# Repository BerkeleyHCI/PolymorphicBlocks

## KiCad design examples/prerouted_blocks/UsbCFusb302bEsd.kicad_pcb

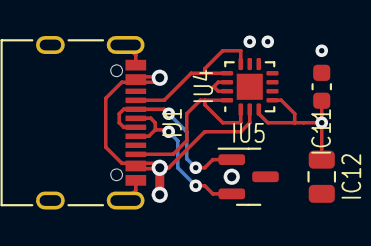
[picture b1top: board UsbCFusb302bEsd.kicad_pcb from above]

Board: 2 copper layers, 5 parts (0 on the bottom side), 8 nets.

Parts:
IC11: C_0603_1608Metric
IC12: C_0805_2012Metric
IJ1: COM-15111 (Sparkfun); USB_C_Receptacle_XKB_U262-16XN-4BVC11
IU4: FUSB302B11MPX (ON Semiconductor); WQFN-14-1EP_2.5x2.5mm_P0.5mm_EP1.45x1.45mm
IU5: PESD5V0X1BT (Nexperia); SOT-23

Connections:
Ignd: IC11.2, IC12.2, IJ1.A1, IJ1.A12, IJ1.B1, IJ1.B12, IJ1.S1, IU4.8, IU4.9, IU4.15, IU5.3
Ipd.ic.vconn: IU4.12, IU4.13
Iusb.A5: IJ1.A5, IU4.10, IU4.11
Iusb.B5: IJ1.B5, IU4.1, IU4.14
Iusb_chain_0.d_N: IJ1.A7, IJ1.B7, IU5.1
Iusb_chain_0.d_P: IJ1.A6, IJ1.B6, IU5.2
Iv3v3: IC11.1, IC12.1, IU4.3, IU4.4
Ivusb: IJ1.A4, IJ1.A9, IJ1.B4, IJ1.B9, IU4.2

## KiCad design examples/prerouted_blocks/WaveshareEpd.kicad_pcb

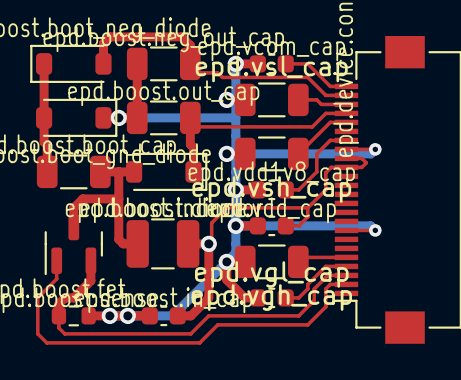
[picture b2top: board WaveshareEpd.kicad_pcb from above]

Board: 2 copper layers, 18 parts (0 on the bottom side), 14 nets.

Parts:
epd.boost.boot_cap, epd.boost.neg_out_cap, epd.boost.out_cap, epd.vgh_cap, epd.vsh_cap, epd.vsl_cap: C_1206_3216Metric
epd.boost.boot_gnd_diode, epd.boost.boot_neg_diode, epd.boost.diode: B5817W (Guangdong Hottech) - 20V 450mV@1A 300mA S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; D_SOD-123
epd.boost.fet: AO3400A (Alpha & Omega Semicon) - 30V 5.7A 26.5m?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; SOT-23
epd.boost.in_cap, epd.vcom_cap, epd.vdd1v8_cap, epd.vdd_cap, epd.vgl_cap: C_0603_1608Metric
epd.boost.inductor: L_1210_3225Metric
epd.boost.sense: R_0603_1608Metric
epd.device.conn: AFC01-S24FCA-00 (Jushuo); Hirose_FH12-24S-0.5SH_1x24-1MP_P0.50mm_Horizontal

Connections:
epd.boost.boot_cap.neg: epd.boost.boot_cap.2, epd.boost.boot_gnd_diode.2, epd.boost.boot_neg_diode.1
epd.boost.inductor.b: epd.boost.boot_cap.1, epd.boost.diode.2, epd.boost.fet.3, epd.boost.inductor.2
epd.boost.neg_out: epd.boost.boot_neg_diode.2, epd.boost.neg_out_cap.2, epd.device.conn.23
epd.boost.pos_out: epd.boost.diode.1, epd.boost.out_cap.1, epd.device.conn.21
epd.device.gdr: epd.boost.fet.1, epd.device.conn.2
epd.device.rese: epd.boost.fet.2, epd.boost.sense.1, epd.device.conn.3
epd.device.vcom: epd.device.conn.24, epd.vcom_cap.1
epd.device.vdd1v8: epd.device.conn.18, epd.vdd1v8_cap.1
epd.device.vgh: epd.device.conn.5, epd.vgh_cap.1
epd.device.vgl: epd.device.conn.4, epd.vgl_cap.2
epd.device.vsh: epd.device.conn.20, epd.vsh_cap.1
epd.device.vsl: epd.device.conn.22, epd.vsl_cap.2
gnd: epd.boost.boot_gnd_diode.1, epd.boost.in_cap.2, epd.boost.neg_out_cap.1, epd.boost.out_cap.2, epd.boost.sense.2, epd.device.conn.8, epd.device.conn.17, epd.vcom_cap.2, epd.vdd1v8_cap.2, epd.vdd_cap.2, epd.vgh_cap.2, epd.vgl_cap.1, epd.vsh_cap.2, epd.vsl_cap.1
v3v3: epd.boost.in_cap.1, epd.boost.inductor.1, epd.device.conn.15, epd.device.conn.16, epd.vdd_cap.1

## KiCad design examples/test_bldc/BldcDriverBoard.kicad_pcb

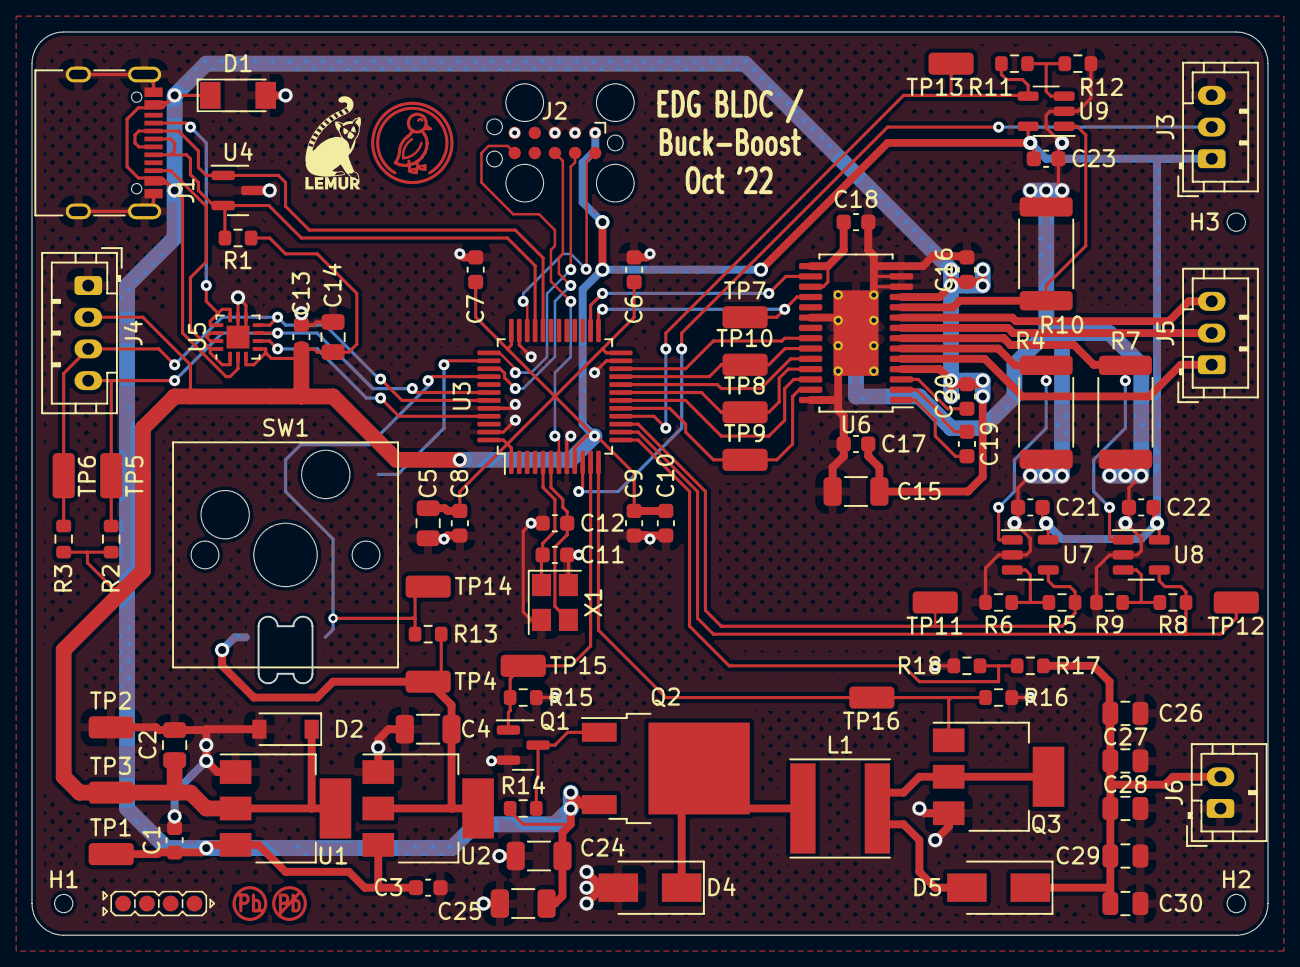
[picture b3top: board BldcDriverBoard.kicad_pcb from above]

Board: 2 copper layers, 78.0 x 57.0 mm, 97 parts (0 on the bottom side), 52 nets.

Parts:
C1, C3, C6, C7, C8, C13, C16, C17, C20, C21, C22, C23: C14663; C_0603_1608Metric
C2, C5: C1779; C_0805_2012Metric
C4: C29823; C_1206_3216Metric
C9, C19: C57112; C_0603_1608Metric
C10: C15849; C_0603_1608Metric
C11, C12: C1663; C_0603_1608Metric
C14: C15850; C_0805_2012Metric
C15, C24, C25: C12891; C_1206_3216Metric
C18: C1623; C_0603_1608Metric
C26, C27, C28, C29, C30: C440198; C_0805_2012Metric
D1: C8078; D_MiniMELF
D2: C499796; D_SOD-123
D3: LED_SK6812MINI-E
D4, D5: C8678; D_SMA
H1, H2, H3: JlcToolingHole_1.152mm
J1: C165948; USB_C_Receptacle_XKB_U262-16XN-4BVC11
J2: Tag-Connect_TC2050-IDC-FP_2x05_P1.27mm_Vertical
J3, J5: JST_PH_B3B-PH-K_1x03_P2.00mm_Vertical
J4: JST_PH_B4B-PH-K_1x04_P2.00mm_Vertical
J6: JST_PH_B2B-PH-K_1x02_P2.00mm_Vertical
L1: C497840; L_Taiyo-Yuden_NR-60xx
Q1: C8545; SOT-23
Q2: C28969; TO-252-2
Q3: C508453; SOT-223-3_TabPin2
R1: C22843; R_0603_1608Metric
R2, R3: C23162; R_0603_1608Metric
R4, R7, R10: C458727; R_2512_6332Metric
R5, R8, R11: C23150; R_0603_1608Metric
R6, R9, R12: C4184; R_0603_1608Metric
R13, R14: C25804; R_0603_1608Metric
R15, R16, R18: C21190; R_0603_1608Metric
R17: C25981; R_0603_1608Metric
SW1: SW_Hotswap_Kailh_MX
TP1, TP2, TP3, TP4, TP5, TP6, TP7, TP8, TP9, TP10, TP11, TP12, TP13, TP14, TP15, TP16: C238130; TestPoint_TE_RCT_0805
U1: C86781; SOT-223-3_TabPin2
U2: C134077; SOT-223-3_TabPin2
U3: C8734; LQFP-48_7x7mm_P0.5mm
U4: C87911; SOT-23
U5: C132291; WQFN-14-1EP_2.5x2.5mm_P0.5mm_EP1.45x1.45mm
U6: C92482; HTSSOP-28-1EP_4.4x9.7mm_P0.65mm_EP2.85x5.4mm_ThermalVias
U7, U8, U9: C7972; SOT-23-5
U10: Symbol_Duckling
U11: Symbol_LemurSmall
U12: Indicator_LeadFree
U13: Indicator_IdDots_4
X1: C9002; Crystal_SMD_3225-4Pin_3.2x2.5mm

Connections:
bldc.phases.2: J5.2, U6.8
bldc.phases.3: J5.3, U6.9
bldc_drv.(adapter)ic.v3p3.src: C18.1, U6.15, U6.17
bldc_drv.ens.1: U3.18, U6.26
bldc_drv.ens.2: U3.20, U6.24
bldc_drv.ic.cph: C19.1, U6.2
bldc_drv.ic.cpl: C19.2, U6.1
bldc_drv.ic.vcp: C20.1, U6.3
bldc_drv.ins.1: TP9.1, U3.17, U6.27
bldc_drv.outs.1: J5.1, U6.5
bldc_drv.pgnds.1: R4.2, U6.6, U7.1
bldc_drv.pgnds.2: R7.2, U6.7, U8.1
bldc_drv.pgnds.3: R10.2, U6.10, U9.1
conv.in_high_switch.(adapter)pre.drain.src: Q1.3, Q2.1, R14.2
conv.in_low_diode.cathode: D4.1, L1.1, Q2.2
conv.out_high_diode.anode: D5.2, L1.2, Q3.2
conv_out.pins.2: C26.1, C27.1, C28.1, C29.1, C30.1, D5.1, J6.2, R17.1
curr_amp[1].amp.inn: R5.2, R6.1, U7.3
curr_amp[2].r1.b: R8.2, R9.1, U8.3
curr_amp[3].(adapter)r2.a.dst: R11.2, R12.1, U9.3
gnd: C1.2, C2.2, C3.2, C4.2, C5.2, C6.2, C7.2, C8.2, C9.2, C10.2, C11.2, C12.2, C13.2, C14.2, C15.2, C16.2, C17.2, C18.2, C21.2, C22.2, C23.2, C24.2, C25.2, C26.2, C27.2, C28.2, C29.2, C30.2, D1.2, D2.2, D3.3, D4.2, J1.A1, J1.A12, J1.B1, J1.B12, J1.S1, J2.2, J2.3, J2.5, J3.3, J4.1, J6.1, Q1.2, Q3.3, R4.1, R6.2, R7.1, R9.2, R10.1, R12.2, R15.1, R16.1, R18.2, SW1.1, TP2.1, U1.1, U2.1, U3.8, U3.23, U3.35, U3.44, U3.47, U4.3, U5.8, U5.9, U5.15, U6.12, U6.13, U6.14, U6.20, U6.28, U6.29, U7.2, U8.2, U9.2, X1.2, X1.4
i2c.i2c.sda: J4.3, R3.2, TP6.1, U3.43, U5.7
i2c_tp.io.scl: J4.4, R2.2, TP5.1, U3.42, U5.6
mag.pins.2: J3.2, U3.10
mcu.adc.conv_sense: R17.2, R18.1, U3.13
mcu.adc.curr_1: R5.1, TP11.1, U3.15, U7.4
mcu.adc.curr_2: R8.1, TP12.1, U3.14, U8.4
mcu.adc.curr_3: R11.1, TP13.1, U3.16, U9.4
mcu.crystal.crystal.a: C11.1, U3.5, X1.1
mcu.crystal.crystal.b: C12.1, U3.6, X1.3
mcu.gpio.bldc_en_3: U3.22, U6.22
mcu.gpio.bldc_fault: TP7.1, U3.25, U6.18
mcu.gpio.bldc_in_2: TP8.1, U3.19, U6.25
mcu.gpio.bldc_in_3: TP10.1, U3.21, U6.23
mcu.gpio.bldc_reset: U3.26, U6.16
mcu.gpio.boost_pwm: Q3.1, R16.2, TP16.1, U3.12
mcu.gpio.buck_pwm: Q1.1, R15.2, TP15.1, U3.11
mcu.gpio.pd_int: U3.45, U5.5
mcu.gpio.rgb: D3.4, R13.2, TP14.1, U3.40
mcu.gpio.sw1: SW1.2, U3.38
mcu.ic.swd.swdio: J2.10, U3.34
mcu.swd.swd.reset: J2.6, U3.7
mcu.swd.swd.swclk: J2.9, U3.37
mcu.swd.swd.swo: J2.8, U3.39
pd.ic.vconn: U5.12, U5.13
usb.cc.cc1: J1.A5, U5.10, U5.11
usb.cc.cc2: J1.B5, U5.1, U5.14
usb.usb.dp: J1.A6, J1.B6, R1.2, U3.33, U4.2
usb_esd.usb.dm: J1.A7, J1.B7, U3.32, U4.1
v3v3: C2.1, C5.1, C6.1, C7.1, C8.1, C9.1, C10.1, C13.1, C14.1, C21.1, C22.1, C23.1, D2.1, J2.1, J3.1, J4.2, R1.1, R2.1, R3.1, TP3.1, U1.2, U3.1, U3.9, U3.24, U3.36, U3.48, U5.3, U5.4, U7.5, U8.5, U9.5
v5: C4.1, D3.1, R13.1, TP4.1, U2.2
vusb: C1.1, C3.1, C15.1, C16.1, C17.1, C20.2, C24.1, C25.1, D1.1, J1.A4, J1.A9, J1.B4, J1.B9, Q2.3, R14.1, TP1.1, U1.3, U2.3, U5.2, U6.4, U6.11

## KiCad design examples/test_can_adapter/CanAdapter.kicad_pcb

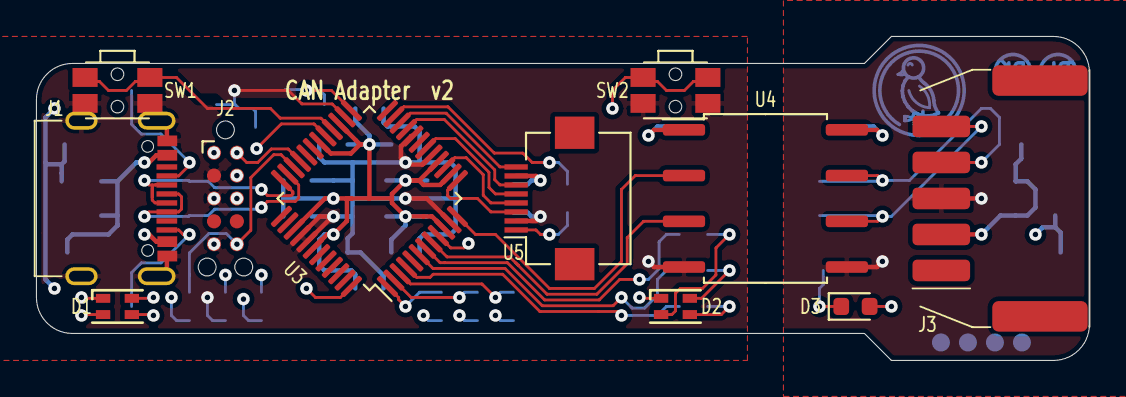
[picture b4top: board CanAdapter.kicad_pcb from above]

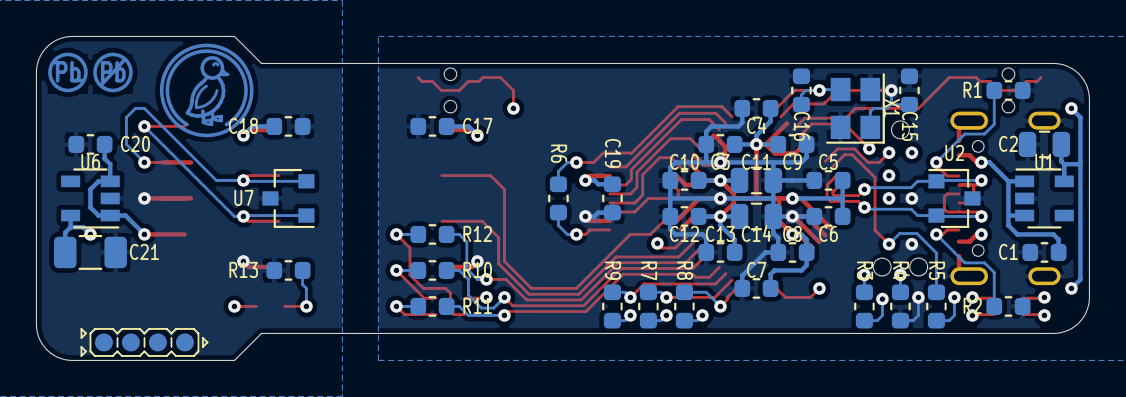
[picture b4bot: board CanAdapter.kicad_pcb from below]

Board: 4 copper layers, 58.5 x 18.0 mm, 53 parts (42 on the bottom side), 42 nets.

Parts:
1: LeadFree; Indicator_LeadFree
2: IdDots4; Indicator_IdDots_4
C1, C19: CL10A105KP8NNNC (Samsung Electro-Mechanics) - 1µF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; C_0603_1608Metric
C2: CL21B225KPFNNNE (Samsung Electro-Mechanics) - 2.2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; C_0805_2012Metric
C3, C5, C7, C9, C10, C12, C13, C17, C18: CL10B104KB8NNNC (Samsung Electro-Mechanics) - 0.1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; C_0603_1608Metric
C4, C6, C8: CL10B103KB8NNNC (Samsung Electro-Mechanics) - 100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; C_0603_1608Metric
C11, C14: CL21A106KPFNNNE (Samsung Electro-Mechanics) - 10µ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; C_0805_2012Metric
C15, C16: CC0603GRNPO9BN180 (Yageo) - 18pF, 50V; C_0603_1608Metric
C20: CL10A105KA8NNNC (Samsung Electro-Mechanics) - 1µF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; C_0603_1608Metric
C21: CL31B225KOHNNNE (Samsung Electro-Mechanics) - 2.2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; C_1206_3216Metric
D1, D2: EAST1616RGBB2 (Everlight Electronics Co Ltd); LED_RGB_0606
D3: LED; LED_0603_1608Metric
J1: COM-15111 (Sparkfun); USB_C_Receptacle_BSC_A40-00119
J2: SWD; Tag-Connect_TC2050-IDC-NL_2x05_P1.27mm_Vertical
J3: 5023520500 (Molex); Molex_DuraClik_502352_1x05_P2.00mm_Horizontal
R1, R2: 5.1k, 1%, 0.1W; R_0603_1608Metric
R3, R4, R5: 10k, 1%, 0.1W; R_0603_1608Metric
R6: 100, 1%, 0.1W; R_0603_1608Metric
R7, R8, R9, R10, R11, R12, R13: 1k, 1%, 0.1W; R_0603_1608Metric
SW1, SW2: EVQ-P7C01P; SW_SPST_EVQP7C
U1: AP2204K-3.3 (Diodes Incorporated); SOT-23-5
U2: TPD2E009 (Texas Instruments); SOT-23
U3: LPC1549JBD48 (NXP); LQFP-48_7x7mm_P0.5mm
U4: ISO1050DUB (Texas Instruments); SOP-8_6.62x9.15mm_P2.54mm
U5: QT096T_IF09, FH12-8S-0.5SH(55); Hirose_FH12-8S-0.5SH_1x08-1MP_P0.50mm_Horizontal
U6: AP2204K-5.0 (Diodes Incorporated); SOT-23-5
U7: PESD1CAN,215; SOT-23
U8: Duck; Symbol_Duckling
X1: 7V-12.000MAHE-T (TXC); Oscillator_SMD_Abracon_ASE-4Pin_3.2x2.5mm

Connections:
can.differential.canl: J3.5, U4.6, U7.1
can_esd.can.canh: J3.4, U4.7, U7.2
can_gnd: C18.2, C20.2, C21.2, J3.3, R13.2, U4.5, U6.2, U7.3
can_reg.pwr_out: C18.1, C21.1, D3.2, U4.8, U6.5
can_vcan: C20.1, J3.2, U6.1, U6.3
crystal.crystal.a: C15.1, U3.26, X1.1
crystal.crystal.b: C16.1, U3.25, X1.3
gnd: C1.2, C2.2, C3.2, C4.2, C5.2, C6.2, C7.2, C8.2, C9.2, C10.2, C11.2, C12.2, C13.2, C14.2, C15.2, C16.2, C17.2, C19.2, J1.A1B12, J1.B1A12, J1.S, J2.2, J2.3, J2.5, R1.1, R2.1, R4.1, SW1.1, SW2.1, U1.2, U2.3, U3.11, U3.17, U3.20, U3.40, U3.41, U4.4, U5.2, X1.2, X1.4
lcd.led: R6.1, U3.23
lcd.led_res.b: R6.2, U5.1
led_can.res.a: D3.1, R13.1
mcu.can_0.rxd: U3.12, U4.2
mcu.can_0.txd: U3.8, U4.3
mcu.digital_12: R10.2, U3.6
mcu.digital_13: R9.2, U3.3
mcu.digital_15: R7.2, U3.2
mcu.digital_16: U3.22, U5.8
mcu.digital_17: U3.15, U5.4
mcu.digital_18: U3.13, U5.3
mcu.spi_1.mosi: U3.18, U5.5
mcu.spi_1.sck: U3.21, U5.6
mcu.swd.reset: J2.6, R5.2, U3.34
mcu.swd.swclk: J2.9, R4.2, U3.29
mcu.swd.swdio: J2.10, R3.2, U3.33
mcu.swd.swo: J2.8, U3.9
rgb_can.blue: R12.2, U3.7
rgb_can.blue_res.a: D2.2, R12.1
rgb_can.green: R11.2, U3.4
rgb_can.package.green_k: D2.3, R11.1
rgb_can.red_res.a: D2.4, R10.1
rgb_usb.green: R8.2, U3.1
rgb_usb.package.blue_k: D1.2, R9.1
rgb_usb.package.green_k: D1.3, R8.1
rgb_usb.package.red_k: D1.4, R7.1
sw_can.out: SW2.2, U3.48
sw_usb.a: SW1.2, U3.28
usb.port.A5: J1.A5, R1.2
usb.port.B5: J1.B5, R2.2
usb_net.d_N: J1.A7, J1.B7, U2.1, U3.36
usb_net.d_P: J1.A6, J1.B6, U2.2, U3.35
v3v3: C2.1, C3.1, C4.1, C5.1, C6.1, C7.1, C8.1, C9.1, C10.1, C11.1, C12.1, C13.1, C14.1, C17.1, C19.1, D1.1, D2.1, J2.1, R3.1, R5.1, U1.5, U3.10, U3.14, U3.16, U3.27, U3.30, U3.39, U3.42, U4.1, U5.7
vusb: C1.1, J1.A4B9, J1.B4A9, U1.1, U1.3

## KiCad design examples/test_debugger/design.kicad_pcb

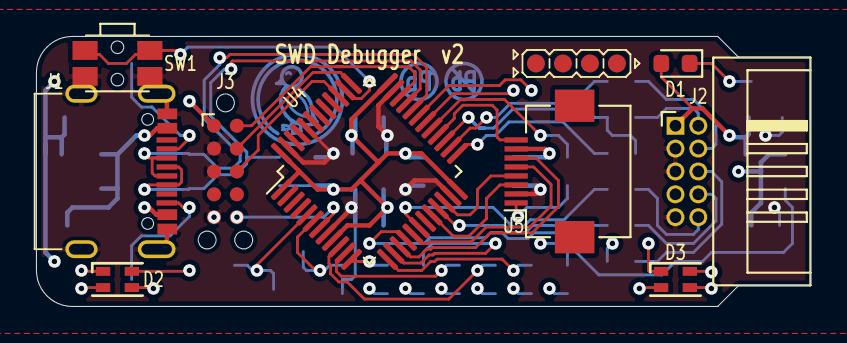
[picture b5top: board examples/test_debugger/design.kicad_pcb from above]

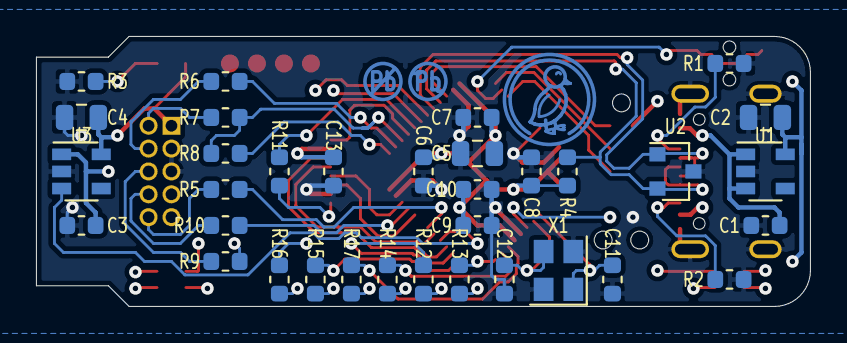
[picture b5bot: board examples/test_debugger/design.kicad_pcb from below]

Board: 4 copper layers, 43.0 x 15.0 mm, 46 parts (36 on the bottom side), 47 nets.

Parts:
1: LeadFree; Indicator_LeadFree
2: IdDots4; Indicator_IdDots_4
C1, C3, C10, C13: CL10A105KP8NNNC (Samsung Electro-Mechanics) - 1µF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; C_0603_1608Metric
C2, C4: CL21B225KPFNNNE (Samsung Electro-Mechanics) - 2.2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; C_0805_2012Metric
C5: CL21A475KQFNNNG (Samsung Electro-Mechanics) - 4.7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; C_0805_2012Metric
C6, C7, C8: CL10B104KB8NNNC (Samsung Electro-Mechanics) - 0.1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; C_0603_1608Metric
C9: CL10B103KB8NNNC (Samsung Electro-Mechanics) - 100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; C_0603_1608Metric
C11, C12: CC0603GRNPO9BN180 (Yageo) - 18pF, 50V; C_0603_1608Metric
D1: LED; LED_0603_1608Metric
D2, D3: EAST1616RGBB2 (Everlight Electronics Co Ltd); LED_RGB_0606
J1: COM-15111 (Sparkfun); USB_C_Receptacle_BSC_A40-00119
J2: 3220-10-0200-00 (CNC Tech) - SWD; PinHeader_2x05_P1.27mm_Horizontal_Shrouded
J3: SWD; Tag-Connect_TC2050-IDC-NL_2x05_P1.27mm_Vertical
R1, R2: 5.1k, 1%, 0.1W; R_0603_1608Metric
R3, R12, R13, R14, R15, R16, R17: 1k, 1%, 0.1W; R_0603_1608Metric
R4: 1.5k, 1%, 0.1W; R_0603_1608Metric
R5, R6, R7, R9, R10: 22, 1%, 0.1W; R_0603_1608Metric
R8, R11: 100, 1%, 0.1W; R_0603_1608Metric
SW1: EVQ-P7C01P; SW_SPST_EVQP7C
U1, U3: AP2204K-3.3 (Diodes Incorporated); SOT-23-5
U2: TPD2E009 (Texas Instruments); SOT-23
U4: STM32F103xxT6 (STMicroelectronics); LQFP-48_7x7mm_P0.5mm
U5: QT096T_IF09, FH12-8S-0.5SH(55); Hirose_FH12-8S-0.5SH_1x08-1MP_P0.50mm_Horizontal
U6: Duck; Symbol_Duckling
X1: 7V-12.000MAHE-T (TXC); Oscillator_SMD_Abracon_ASE-4Pin_3.2x2.5mm

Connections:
(adapter)tdi_res.a.dst: R10.1, U4.21
crystal.crystal.b: C12.1, U4.6, X1.3
gnd: C1.2, C2.2, C3.2, C4.2, C5.2, C6.2, C7.2, C8.2, C9.2, C10.2, C11.2, C12.2, C13.2, J1.A1B12, J1.B1A12, J1.S, J2.3, J2.5, J2.9, J3.2, J3.3, J3.5, R1.1, R2.1, R3.2, SW1.1, U1.2, U2.3, U3.2, U4.8, U4.23, U4.35, U4.44, U4.47, U5.2, X1.2, X1.4
lcd.cs: U4.28, U5.8
lcd.device.leda: R11.2, U5.1
lcd.reset: U4.20, U5.3
lcd.rs: U4.22, U5.4
lcd.spi.sck: U4.15, U5.6
led_target.package.k: D1.1, R3.1
led_target.signal: C4.1, D1.2, J2.1, U3.5
mcu.digital_12: SW1.2, U4.38
mcu.digital_13: R17.2, U4.10
mcu.digital_15: R15.2, U4.13
mcu.digital_18: R12.2, U4.14
mcu.digital_22: R11.1, U4.29
mcu.digital_26: R8.1, U4.25
mcu.digital_27: R7.1, R8.2, U4.27
mcu.digital_28: R6.1, U4.26
mcu.spi_0.mosi: U4.17, U5.5
mcu.swd.swdio: J3.10, U4.34
mcu.swd.swo: J3.8, U4.39
mcu.xtal.xtal_in: C11.1, U4.5, X1.1
rgb_tgt.blue_res.a: D3.2, R17.1
rgb_tgt.green: R16.2, U4.30
rgb_tgt.green_res.a: D3.3, R16.1
rgb_tgt.package.red_k: D3.4, R15.1
rgb_usb.blue: R14.2, U4.11
rgb_usb.blue_res.a: D2.2, R14.1
rgb_usb.green: R13.2, U4.12
rgb_usb.green_res.a: D2.3, R13.1
rgb_usb.red_res.a: D2.4, R12.1
swd.swd.reset: J3.6, U4.7
swd.swd.swclk: J3.9, U4.37
target.swd.reset: J2.10, R5.2
target.swd.swdio: J2.2, R7.2
target_drv.reset_in: R5.1, U4.18
target_drv.swd.swclk: J2.4, R6.2
target_drv.swd.swo: J2.6, R9.2
target_drv.swo_out: R9.1, U4.31
target_reg.en: U3.3, U4.16
tdi_res.b: J2.8, R10.2
usb.port.A5: J1.A5, R1.2
usb.port.B5: J1.B5, R2.2
usb_net.d_N: J1.A7, J1.B7, U2.1, U4.32
usb_net.d_P: J1.A6, J1.B6, R4.2, U2.2, U4.33
v3v3: C2.1, C5.1, C6.1, C7.1, C8.1, C9.1, C10.1, C13.1, D2.1, D3.1, J3.1, R4.1, U1.5, U4.1, U4.9, U4.24, U4.36, U4.48, U5.7
vusb: C1.1, C3.1, J1.A4B9, J1.B4A9, U1.1, U1.3, U3.1

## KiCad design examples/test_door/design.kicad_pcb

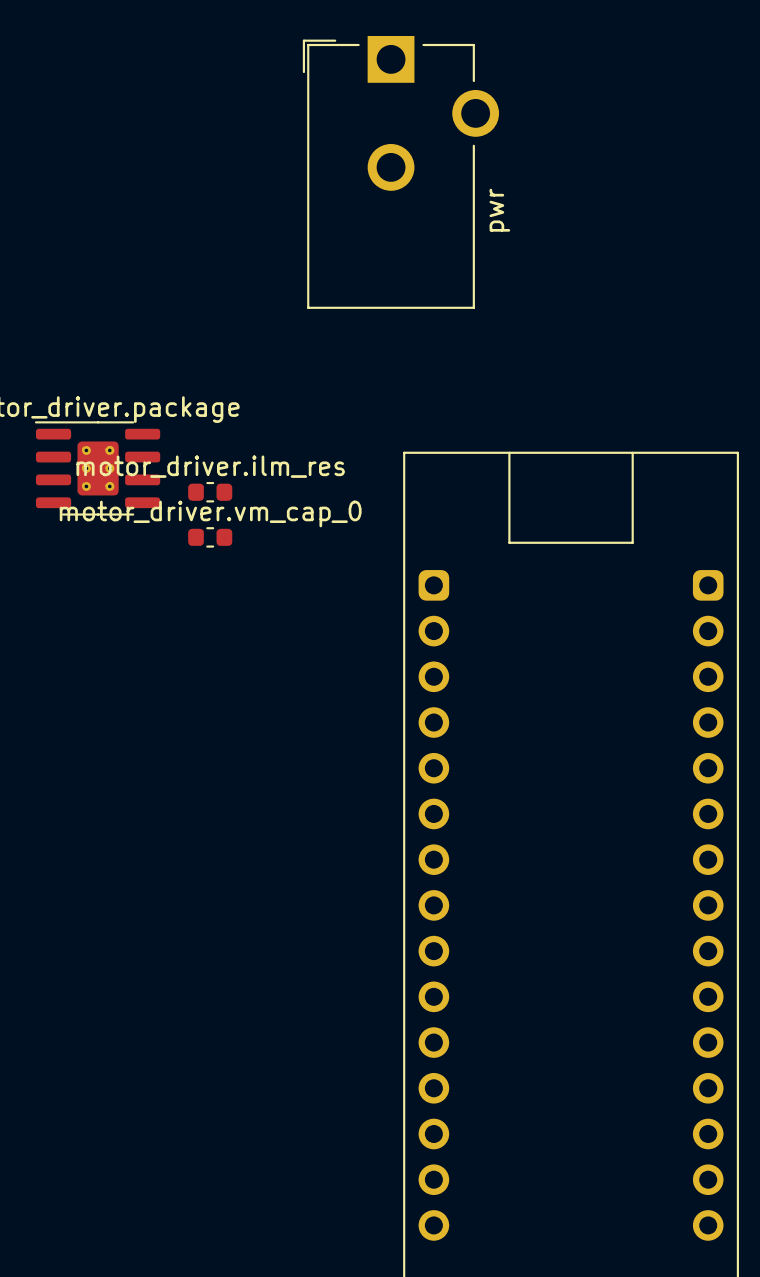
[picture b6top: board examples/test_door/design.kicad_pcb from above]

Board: 2 copper layers, 5 parts (0 on the bottom side), 5 nets, no tracks yet.

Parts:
mcu: Nucleo-F303K8; Nucleo32
motor_driver.ilm_res: 33000, 1%, 0.1W; R_0603_1608Metric
motor_driver.package: DRV8871; SOIC-8-1EP_3.9x4.9mm_P1.27mm_EP2.29x3mm_ThermalVias
motor_driver.vm_cap_0: 0.1µF, 50V, CL10B104KB8NNNC; C_0603_1608Metric
pwr: PJ-102A; BarrelJack_CUI_PJ-102AH_Horizontal

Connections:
mcu.digital_17: mcu.1, motor_driver.package.2
motor_driver.ilm_res.a: motor_driver.ilm_res.1, motor_driver.package.4
motor_driver.in1: mcu.2, motor_driver.package.3
pwr.gnd: mcu.4, mcu.17, motor_driver.ilm_res.2, motor_driver.package.1, motor_driver.package.7, motor_driver.package.9, motor_driver.vm_cap_0.2, pwr.2
pwr.pwr: motor_driver.package.5, motor_driver.vm_cap_0.1, pwr.1

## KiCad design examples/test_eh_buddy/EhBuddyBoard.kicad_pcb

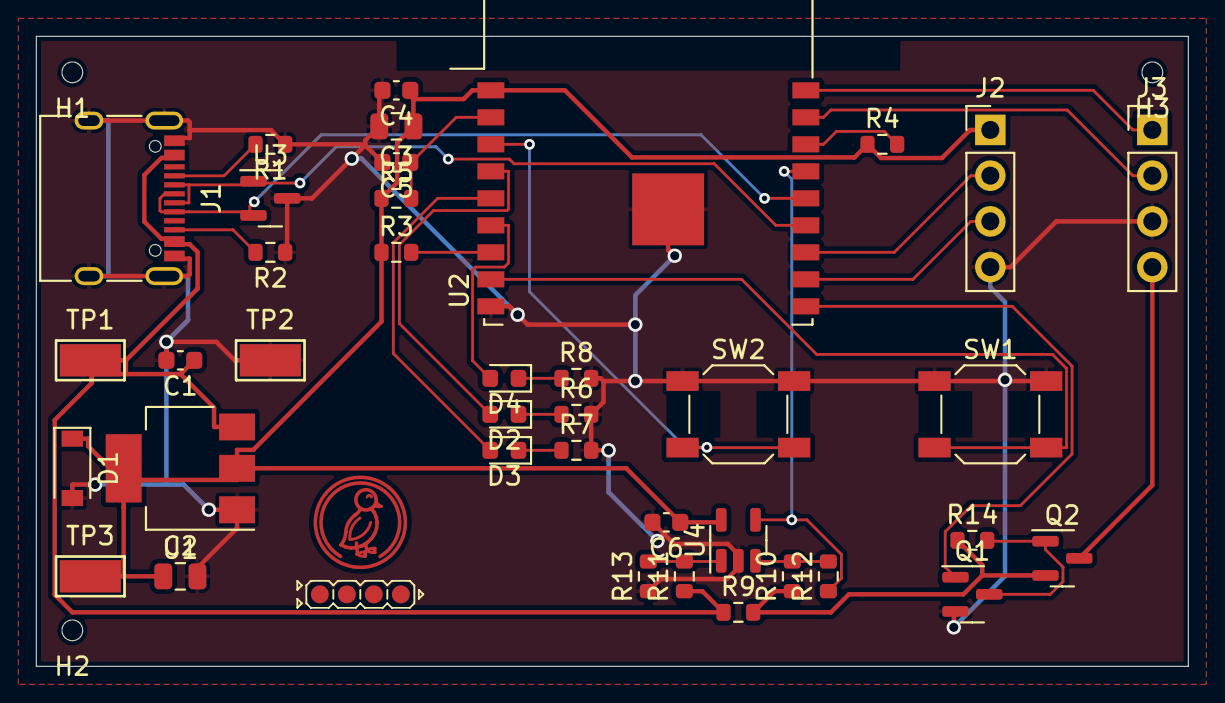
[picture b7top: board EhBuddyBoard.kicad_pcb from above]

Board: 2 copper layers, 64.0 x 35.0 mm, 43 parts (0 on the bottom side), 29 nets.

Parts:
C1, C4, C5, C6: C_0603_1608Metric
C2, C3: C_0805_2012Metric
D1: BZT52C3V6 (SMC(Sangdest Microelectronicstronic (N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; D_SOD-123
D2: KT-0603R (Hubei KENTO Elec) - Red 615~630nm 1.9~2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; LED_0603_1608Metric
D3, D4: LED_0603_1608Metric
H1, H2, H3: JlcToolingHole_1.152mm
J1: COM-15111 (Sparkfun); USB_C_Receptacle_XKB_U262-16XN-4BVC11
J2, J3: PinHeader2.54 1x4 (Generic); PinHeader_1x04_P2.54mm_Vertical
Q1: 2N7002 (Changjiang Electronics Tech (CJ)) - 60V 1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; SOT-23
Q2: AO3401A (Alpha & Omega Semicon) - 30V 4A 44m?@10V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; SOT-23
R1, R2, R3, R4, R5, R6, R7, R8, R9, R10, R11, R12, R13, R14: R_0603_1608Metric
SW1, SW2: 5.1mm switch; SW_SPST_SKQG_WithoutStem
TP1: 5015 (Keystone) - vusb; TestPoint_Keystone_5015_Micro-Minature
TP2: 5015 (Keystone) - gnd; TestPoint_Keystone_5015_Micro-Minature
TP3: 5015 (Keystone) - v3v3; TestPoint_Keystone_5015_Micro-Minature
U1: LD1117S33TR (STMicroelectronics); SOT-223-3_TabPin2
U2: ESP32-C3-WROOM-02 (Espressif Systems); ESP-WROOM-02
U3: PESD5V0X1BT (Nexperia); SOT-23
U4: LMV321 (Texas Instruments); SOT-23-5
U5: Duck; Symbol_Duckling
U6: IdDots4; Indicator_IdDots_4

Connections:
conn.uart.rx: J3.1, U2.18
conn.uart.tx: J3.2, U2.17
gnd: C1.2, C2.2, C3.2, C4.2, C5.2, C6.2, D1.2, J1.A1, J1.A12, J1.B1, J1.B12, J1.S1, J2.4, J3.3, Q1.2, R1.1, R2.1, R6.2, R7.2, R8.2, R13.1, SW1.1, SW2.1, TP2.1, U1.1, U2.9, U2.19, U3.3, U4.2
isense.amp.r1.b: R10.2, R12.2, U4.3
isense.amp.r2.b: R11.2, R13.2, U4.1
isense.out: R12.1, U2.15, U4.4
isense.pwr_out: Q2.2, R9.2, R10.1, R14.1
ledb.res.a: D4.1, R8.1
ledb.signal: D4.2, U2.6
ledg.res.a: D3.1, R7.1
ledg.signal: D3.2, U2.5
ledr.res.a: D2.1, R6.1
ledr.signal: D2.2, U2.4
mcu.ic.en: C5.1, R5.2, U2.2
mcu.ic.io2: R4.2, U2.16
mcu.ic.io8: R3.2, U2.7
mcu.prog.out: SW1.2, U2.8
mcu.uart0.uart.rx: J2.2, U2.12
mcu.uart0.uart.tx: J2.3, U2.11
sw1.out: SW2.2, U2.3
sw.control: Q1.1, U2.10
sw.output: J3.4, Q2.3
sw.pre.drain: Q1.3, Q2.1, R14.2
usb.conn.A5: J1.A5, R1.2
usb.conn.B5: J1.B5, R2.2
usb.usb.dm: J1.A7, J1.B7, U2.13, U3.1
usb.usb.dp: J1.A6, J1.B6, U2.14, U3.2
v3v3: C2.1, C3.1, C4.1, C6.1, D1.1, J2.1, R3.1, R4.1, R5.1, TP3.1, U1.2, U2.1, U4.5
vusb: C1.1, J1.A4, J1.A9, J1.B4, J1.B9, R9.1, R11.1, TP1.1, U1.3

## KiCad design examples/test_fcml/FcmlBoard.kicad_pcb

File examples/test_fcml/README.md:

Programming
- Programming the FPGA: use [Diamond Programmer](https://www.latticesemi.com/programmer)
  - If using a FT232H-based programmer, set the Cable to HW-USBN-2B
  - For SPI flash programming: the CS jumper must be soldered closed
  - It will not auto-detect connected devices, so set the entry manually:
    - Device Family: iCE40 UltraPlus
    - Device: iCE40UP5K
  - Set the SPI flash
    - _Diamond Programmer does not have the W25Q128JV series, so we're going to configure it for a different but compatible 128M flash_  
    - Right click the device entry > Device Properties
    - SPI Flash Family: SPI Serial Flash
    - Vendor: Micron
    - Device: SPI-M25P128
    - Package: doesn't matter
  - Select a bitstream and program
- Programming the RP2040
  - SWD: TODO
  - USB: connect to the USB, drag-and-drop a .uf2 file to the flash drive
    - If the flash drive does not show up: this may be because of non-empty flash.
      The stock dev board has a BOOTSEL button to force USB bootloader by shorting the flash CS low.
      Shorting CS low here (eg, by a IC clip attached to the flash chip's pin) does the same thing here.
      The flash can then be erased by flashing [flash_nuke.uf2](https://www.raspberrypi.com/documentation/microcontrollers/raspberry-pi-pico.html#resetting-flash-memory). 
    
Errata for v1
- RP2040 does not run code from flash - perhaps it needs all 4 QSPI IO pins?
- RP2040 does not debug with CMSIS-DAP

Potential improvements for v2
- Converter in connectors: rotated 90 degrees, balanced lengths to V+ and V-
- Bootstrap diodes: rotated 90 so they're not protruding into the converter power path pour
- Maybe move decoupling caps closer to FPGA and MCU
- Decoupling cap 1uF on USB Vbus line, as transient suppression

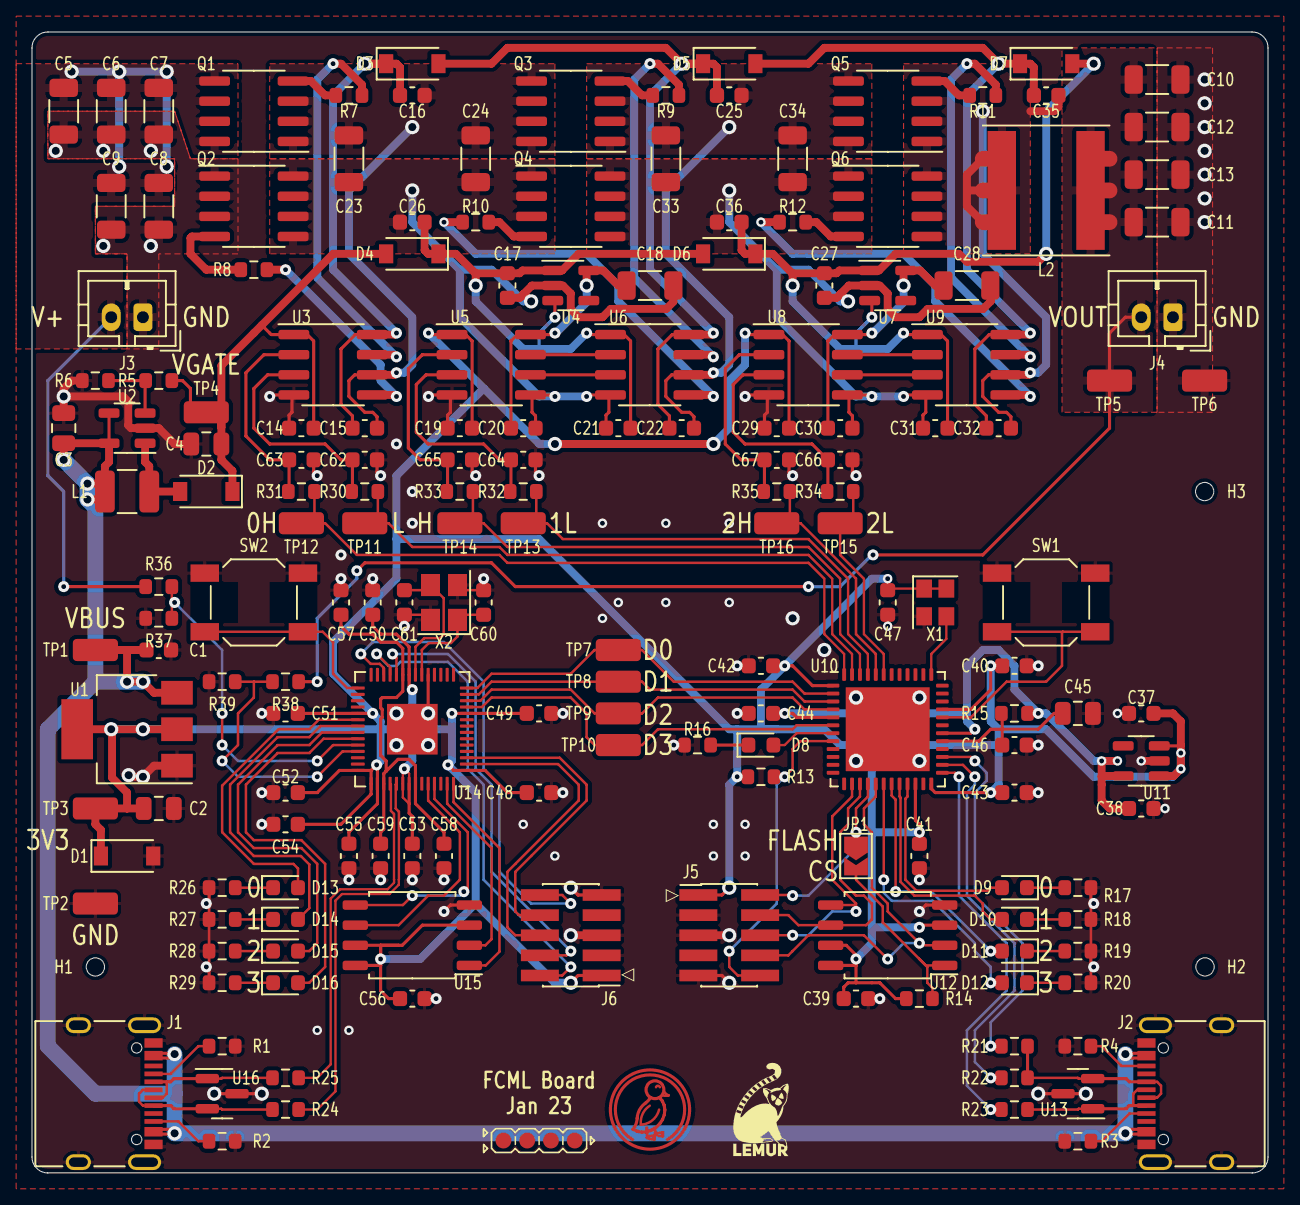
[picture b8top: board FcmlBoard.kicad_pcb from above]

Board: 2 copper layers, 78.0 x 72.0 mm, 179 parts (0 on the bottom side), 108 nets.

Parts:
C1, C14, C15, C16, C17, C19, C20, C21, C22, C25, C26, C27, C29, C30, C31, C32, C35, C36, C37, C38, C39, C40, C41, C42, C43, C44, C46, C47, C48, C49, C50, C51, C52, C53, C54, C55, C56, C57, C58, C59, C60, C61, C62, C63, C64, C65, C66, C67: C_0603_1608Metric
C2, C3, C4, C45: C_0805_2012Metric
C5, C6, C7, C8, C9, C10, C11, C12, C13, C18, C23, C24, C28, C33, C34: C_1206_3216Metric
D1: BZT52C3V6 (SMC(Sangdest Microelectronicstronic (N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; D_SOD-123
D2: B0520W (Shikues) - 20V 390mV@500mA 500mA SOD-123 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; D_SOD-123
D3, D4, D5, D6, D7: B5819W SL (Changjiang Electronics Tech (CJ)) - 40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; D_SOD-123
D8, D9, D10, D11, D12, D13, D14, D15, D16: KT-0603R (Hubei KENTO Elec) - Red 615~630nm 1.9~2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; LED_0603_1608Metric
H1, H2, H3: JlcToolingHole_1.152mm
J1, J2: COM-15111 (Sparkfun); USB_C_Receptacle_XKB_U262-16XN-4BVC11
J3, J4: B2B-PH-K (JST); JST_PH_B2B-PH-K_1x02_P2.00mm_Vertical
J5, J6: PinHeader1.27 Shrouded 2x5 (Generic); PinHeader_2x05_P1.27mm_Vertical_SMD
JP1: SolderJumper-2_P1.3mm_Open_TrianglePad1.0x1.5mm
L1: L_1210_3225Metric
L2: L_Taiyo-Yuden_NR-80xx
Q1, Q2, Q3, Q4, Q5, Q6: HSM4410 (HUASHUO) - 30V 12A 2.5W 9.5m?@10V,12A 2.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; SOIC-8_3.9x4.9mm_P1.27mm
R1, R2, R3, R4, R5, R6, R7, R8, R9, R10, R11, R12, R13, R14, R15, R16, R17, R18, R19, R20, R21, R22, R23, R24, R25, R26, R27, R28, R29, R30, R31, R32, R33, R34, R35, R36, R37, R38, R39: R_0603_1608Metric
SW1, SW2: 5.1mm switch; SW_SPST_SKQG_WithoutStem
TP1: 5015 (Keystone) - vusb; TestPoint_TE_RCT_0805
TP2, TP6: 5015 (Keystone) - gnd; TestPoint_TE_RCT_0805
TP3: 5015 (Keystone) - v3v3; TestPoint_TE_RCT_0805
TP4: 5015 (Keystone) - vgate; TestPoint_TE_RCT_0805
TP5: 5015 (Keystone) - _conv_pwr_out_link; TestPoint_TE_RCT_0805
TP7: 5015 (Keystone) - _mcu_gpio_fpga0_link; TestPoint_TE_RCT_0805
TP8: 5015 (Keystone) - _mcu_gpio_fpga1_link; TestPoint_TE_RCT_0805
TP9: 5015 (Keystone) - _mcu_gpio_fpga2_link; TestPoint_TE_RCT_0805
TP10: 5015 (Keystone) - _mcu_gpio_fpga3_link; TestPoint_TE_RCT_0805
TP11: 5015 (Keystone) - _fpga_gpio_pwm_link.0L; TestPoint_TE_RCT_0805
TP12: 5015 (Keystone) - _fpga_gpio_pwm_link.0H; TestPoint_TE_RCT_0805
TP13: 5015 (Keystone) - _fpga_gpio_pwm_link.1L; TestPoint_TE_RCT_0805
TP14: 5015 (Keystone) - _fpga_gpio_pwm_link.1H; TestPoint_TE_RCT_0805
TP15: 5015 (Keystone) - _fpga_gpio_pwm_link.2L; TestPoint_TE_RCT_0805
TP16: 5015 (Keystone) - _fpga_gpio_pwm_link.2H; TestPoint_TE_RCT_0805
U1: LD1117S33TR (STMicroelectronics); SOT-223-3_TabPin2
U2: AP3012K (Diodes Incorporated); SOT-23-5
U3, U6, U9: IR2301 (Infineon Technologies); SOIC-8_3.9x4.9mm_P1.27mm
U4, U7: AP2204K-3.3 (Diodes Incorporated); SOT-23-5
U5, U8: CBMuD1200L (Corebai); SOIC-8_3.9x4.9mm_P1.27mm
U10: ICE40UP5K-SG48 (Lattice Semiconductor Corporation); QFN-48-1EP_7x7mm_P0.5mm_EP5.3x5.3mm
U11: LP5907MFX-1.2/NOPB (Texas Instruments); SOT-23-5
U12, U15: W25Q128JVSIQ (Winbond Electronics); SOIC-8_5.23x5.23mm_P1.27mm
U13, U16: PGB102ST23 (Littelfuse); SOT-23
U14: RP2040 (Raspberry Pi); QFN-56-1EP_7x7mm_P0.4mm_EP3.2x3.2mm
U17: Duck; Symbol_Duckling
U18: Lemur; Symbol_LemurSmall
U19: IdDots4; Indicator_IdDots_4
X1: Crystal_SMD_2520-4Pin_2.5x2.0mm
X2: Crystal_SMD_3225-4Pin_3.2x2.5mm

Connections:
cdone.res.a: D8.1, R16.1
conv.pwr_in: C5.1, C6.1, C7.1, C8.1, C9.1, J3.2, Q1.5, Q1.6, Q1.7, Q1.8, R36.1
conv.pwr_out: C10.1, C11.1, C12.1, C13.1, J4.2, L2.2, R38.1, TP5.1
conv.sw[0].high_boot_cap.pos: C15.1, C16.1, D3.1, U3.8
conv.sw[0].high_gate_res.a: R7.1, U3.7
conv.sw[0].high_gate_res.b: Q1.4, R7.2
conv.sw[0].low_gate_res.a: R8.1, U3.5
conv.sw[0].low_gate_res.b: Q2.4, R8.2
conv.sw[1].driver.high_in: U5.7, U6.2
conv.sw[1].driver.low_in: U5.6, U6.3
conv.sw[1].high_boot_out: C22.1, C25.1, D3.2, D5.1, U6.8
conv.sw[1].high_gate_res.a: R9.1, U6.7
conv.sw[1].high_gate_res.b: Q3.4, R9.2
conv.sw[1].high_in: C15.2, C16.2, C23.1, C24.1, Q1.1, Q1.2, Q1.3, Q3.5, Q3.6, Q3.7, Q3.8, U3.6
conv.sw[1].iso.pwr_b: C18.1, C20.1, U4.5, U5.8
conv.sw[1].low_gate_res.a: R10.1, U6.5
conv.sw[1].low_gate_res.b: Q4.4, R10.2
conv.sw[1].low_in: C17.2, C18.2, C20.2, C21.2, C23.2, C24.2, C26.2, Q2.5, Q2.6, Q2.7, Q2.8, Q4.1, Q4.2, Q4.3, U4.2, U5.5, U6.4
conv.sw[2].driver.high_in: U8.7, U9.2
conv.sw[2].driver.low_in: U8.6, U9.3
conv.sw[2].high_boot_out: C32.1, C35.1, D5.2, D7.1, U9.8
conv.sw[2].high_gate_res.a: R11.1, U9.7
conv.sw[2].high_gate_res.b: Q5.4, R11.2
conv.sw[2].high_in: C22.2, C25.2, C33.1, C34.1, Q3.1, Q3.2, Q3.3, Q5.5, Q5.6, Q5.7, Q5.8, U6.6
conv.sw[2].iso.pwr_b: C28.1, C30.1, U7.5, U8.8
conv.sw[2].low_boot_in: C17.1, C21.1, C26.1, D4.1, D6.2, U4.1, U4.3, U6.1
conv.sw[2].low_boot_out: C27.1, C31.1, C36.1, D6.1, D7.2, U7.1, U7.3, U9.1
conv.sw[2].low_gate_res.a: R12.1, U9.5
conv.sw[2].low_gate_res.b: Q6.4, R12.2
conv.sw[2].low_in: C27.2, C28.2, C30.2, C31.2, C33.2, C34.2, C36.2, Q4.5, Q4.6, Q4.7, Q4.8, Q6.1, Q6.2, Q6.3, U7.2, U8.5, U9.4
conv.sw[2].low_out: C32.2, C35.2, L2.1, Q5.1, Q5.2, Q5.3, Q6.5, Q6.6, Q6.7, Q6.8, U9.6
conv_in_sense.output: R36.2, R37.1, U14.38
conv_out_sense.output: R38.2, R39.1, U14.39
fpga.cdone: D8.2, U10.7
fpga.cs_jmp.output: JP1.2, R14.2, U12.1
fpga.gpio.led_0: D9.2, U10.21
fpga.gpio.led_1: D10.2, U10.20
fpga.gpio.led_2: D11.2, U10.19
fpga.gpio.led_3: D12.2, U10.18
fpga.gpio.pwm_0H: R31.1, TP12.1, U10.48
fpga.gpio.pwm_0L: R30.1, TP11.1, U10.47
fpga.gpio.pwm_1H: R33.1, TP14.1, U10.46
fpga.gpio.pwm_1L: R32.1, TP13.1, U10.45
fpga.gpio.pwm_2H: R35.1, TP16.1, U10.44
fpga.gpio.pwm_2L: R34.1, TP15.1, U10.43
fpga.ic.creset_b: J5.10, R13.2, U10.8
fpga.ic.spi_config.miso: J5.8, U10.17, U12.2
fpga.ic.spi_config.mosi: J5.6, U10.14, U12.5
fpga.ic.spi_config.sck: J5.4, U10.15, U12.6
fpga.ic.spi_config_cs: J5.2, JP1.1, U10.16
fpga.pll_res.pwr_out: C45.1, C46.1, R15.2, U10.29
fpga.vcc_reg.pwr_out: C38.1, C44.1, R15.1, U10.5, U10.30, U11.5
fpga_led.led[0].res.a: D9.1, R17.1
fpga_led.led[1].res.a: D10.1, R18.1
fpga_led.led[2].res.a: D11.1, R19.1
fpga_led.led[3].res.a: D12.1, R20.1
fpga_osc.out: U10.37, X1.3
fpga_sw.out: SW1.2, U10.32
gnd: C1.2, C2.2, C3.2, C4.2, C5.2, C6.2, C7.2, C8.2, C9.2, C10.2, C11.2, C12.2, C13.2, C14.2, C19.2, C29.2, C37.2, C38.2, C39.2, C40.2, C41.2, C42.2, C43.2, C44.2, C45.2, C46.2, C47.2, C48.2, C49.2, C50.2, C51.2, C52.2, C53.2, C54.2, C55.2, C56.2, C57.2, C58.2, C59.2, C60.2, C61.2, C62.2, C63.2, C64.2, C65.2, C66.2, C67.2, D1.2, J1.A1, J1.A12, J1.B1, J1.B12, J1.S1, J2.A1, J2.A12, J2.B1, J2.B12, J2.S1, J3.1, J4.1, J5.3, J5.5, J5.9, J6.3, J6.5, J6.9, Q2.1, Q2.2, Q2.3, R1.1, R2.1, R3.1, R4.1, R6.2, R16.2, R17.2, R18.2, R19.2, R20.2, R26.2, R27.2, R28.2, R29.2, R37.2, R39.2, SW1.1, SW2.1, TP2.1, TP6.1, U1.1, U2.2, U3.4, U5.4, U8.4, U10.49, U11.2, U12.4, U13.3, U14.19, U14.57, U15.4, U16.3, X1.2, X2.2, X2.4
mcu.crystal.crystal.a: C60.1, U14.20, X2.1
mcu.crystal.crystal.b: C61.1, U14.21, X2.3
mcu.gpio.led_0: D13.2, U14.34
mcu.gpio.led_1: D14.2, U14.35
mcu.gpio.led_2: D15.2, U14.36
mcu.gpio.led_3: D16.2, U14.37
mcu.ic.qspi.miso: U14.55, U15.2
mcu.ic.qspi.mosi: U14.53, U15.5
mcu.ic.qspi.sck: U14.52, U15.6
mcu.ic.qspi_cs: U14.56, U15.1
mcu.ic.vreg_vout: C57.1, C58.1, C59.1, U14.23, U14.45, U14.50
mcu.swd.swd.reset: J6.10, U14.26
mcu.swd.swd.swclk: J6.4, U14.24
mcu.swd.swd.swdio: J6.2, U14.25
mcu.swd.swo: J6.6, U14.2
mcu.swd.tdi: J6.8, U14.3
mcu.usb_chain_0.d_N: R25.1, U14.46
mcu.usb_chain_0.d_P: R24.1, U14.47
mcu_leds.led[0].res.a: D13.1, R26.1
mcu_leds.led[1].res.a: D14.1, R27.1
mcu_leds.led[2].res.a: D15.1, R28.1
mcu_leds.led[3].res.a: D16.1, R29.1
mcu_sw.out: SW2.2, U14.29
reg_vgate.fb.output: R5.2, R6.1, U2.3
reg_vgate.power_path.switch: D2.2, L1.2, U2.1
tp_fpga[0].io: TP7.1, U10.2, U14.14
tp_fpga[1].io: TP8.1, U10.3, U14.13
tp_fpga[2].io: TP9.1, U10.4, U14.12
tp_fpga[3].io: TP10.1, U10.6, U14.11
tp_pwm.output.0H: C63.1, R31.2, U3.2
tp_pwm.output.0L: C62.1, R30.2, U3.3
tp_pwm.output.1H: C65.1, R33.2, U5.2
tp_pwm.output.1L: C64.1, R32.2, U5.3
tp_pwm.output.2H: C67.1, R35.2, U8.2
tp_pwm.output.2L: C66.1, R34.2, U8.3
usb_fpga.conn.A5: J2.A5, R3.2
usb_fpga.conn.B5: J2.B5, R4.2
usb_fpga_bitbang.dm: R23.1, U10.25
usb_fpga_bitbang.dp: R22.1, U10.26
usb_fpga_bitbang.dp_pull: R21.1, U10.27
usb_fpga_chain_0.d_N: J2.A7, J2.B7, R23.2, U13.1
usb_fpga_chain_0.d_P: J2.A6, J2.B6, R21.2, R22.2, U13.2
usb_mcu.conn.A5: J1.A5, R1.2
usb_mcu.conn.B5: J1.B5, R2.2
usb_mcu_chain_0.d_N: J1.A7, J1.B7, R25.2, U16.1
usb_mcu_chain_0.d_P: J1.A6, J1.B6, R24.2, U16.2
v3v3: C2.1, C19.1, C29.1, C37.1, C39.1, C40.1, C41.1, C42.1, C43.1, C47.1, C48.1, C49.1, C50.1, C51.1, C52.1, C53.1, C54.1, C55.1, C56.1, D1.1, J5.1, J6.1, R13.1, R14.1, TP3.1, U1.2, U5.1, U8.1, U10.1, U10.22, U10.24, U10.33, U11.1, U11.3, U12.3, U12.7, U12.8, U14.1, U14.10, U14.22, U14.33, U14.42, U14.43, U14.44, U14.48, U14.49, U15.3, U15.7, U15.8, X1.1, X1.4
vgate: C4.1, C14.1, D2.1, D4.2, R5.1, TP4.1, U3.1
vusb: C1.1, C3.1, J1.A4, J1.A9, J1.B4, J1.B9, J2.A4, J2.A9, J2.B4, J2.B9, L1.1, TP1.1, U1.3, U2.4, U2.5
